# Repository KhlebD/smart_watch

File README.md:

# ESP32-S3 Smartwatch

A DIY smartwatch built from scratch around the ESP32-S3-Zero, with custom PCBs, a round touch display running LVGL, health and environment sensors, and a custom Android companion app.

https://github.com/user-attachments/assets/0c07c2c6-404b-4337-90d6-0c7b8de9bd92

## Features

- Watch face with time, date, battery and BLE status
- Step counter, heart rate, altitude and temperature
- Phone notifications, music controls and run tracking over BLE
- Hebrew (right-to-left) text support
- Wake on wrist motion and swipe navigation

## Hardware

The electronics are split over two round 48 mm PCBs designed in KiCad (in [`hardware/`](hardware/)), and the case is a parametric OpenSCAD model (in [`case/`](case/)). 

## Firmware

Arduino on PlatformIO, with LVGL 8.3.11, LovyanGFX and NimBLE. The watch talks to the phone using the Gadgetbridge / Bangle.js JSON protocol.

To build: open the project in PlatformIO, select the `esp32-s3-zero` environment, then build and upload over USB.

## Companion app

A custom Kotlin Android app syncs the time, forwards notifications, controls music and receives run data. [github/co](https://github.com/KhlebD/watch_app)

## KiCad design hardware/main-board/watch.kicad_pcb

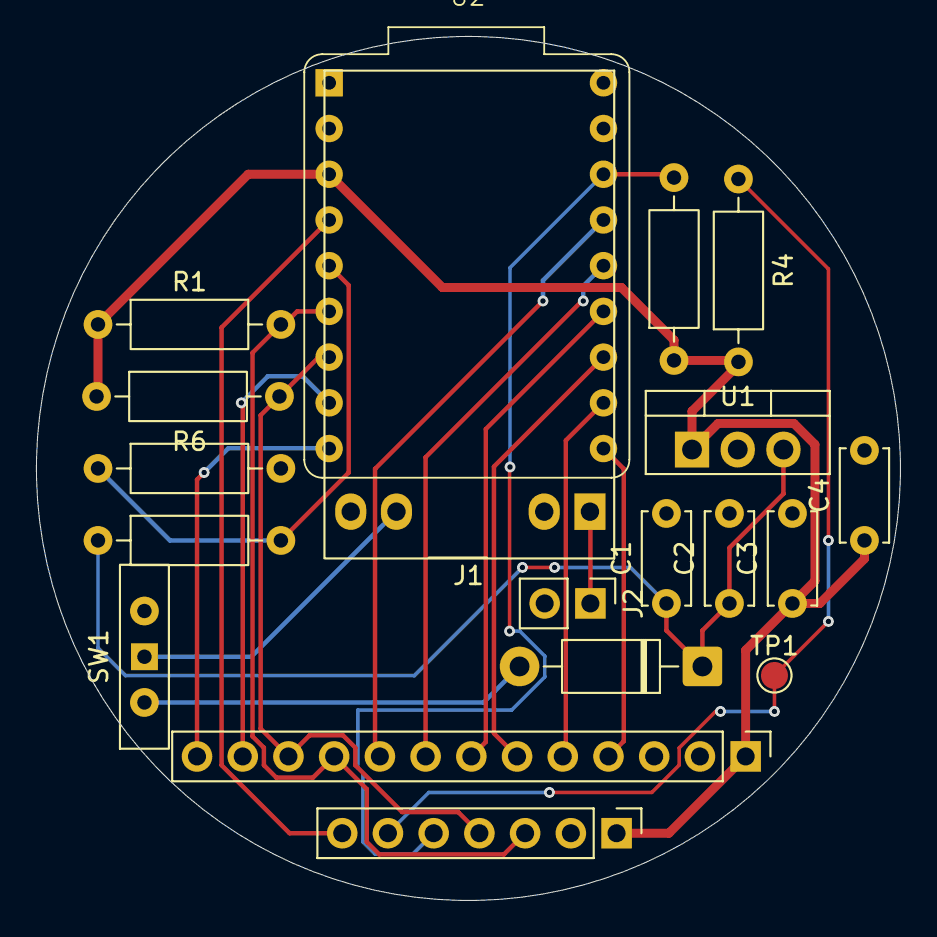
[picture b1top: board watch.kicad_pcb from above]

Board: 2 copper layers, 48.0 x 48.0 mm, 19 parts (0 on the bottom side), 20 nets.

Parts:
C1, C3: 100nF; C_Disc_D5.0mm_W2.5mm_P5.00mm
C2, C4: 10µF; C_Disc_D5.0mm_W2.5mm_P5.00mm
D1: 1N5817; D_DO-41_SOD81_P10.16mm_Horizontal
J1: TP4056; FanPinHeader_1x04_P2.54mm_Vertical
J2: Battery; PinHeader_1x02_P2.54mm_Vertical
J3: To-Sensor-Board; PinHeader_1x07_P2.54mm_Vertical
J5: GC9A01+CST816S; PinHeader_1x13_P2.54mm_Vertical
R1, R2, R3, R4: 5.1k; R_Axial_DIN0207_L6.3mm_D2.5mm_P10.16mm_Horizontal
R5, R6: 100k; R_Axial_DIN0207_L6.3mm_D2.5mm_P10.16mm_Horizontal
SW1: SS12D00; SW_Slide-03_Wuerth-WS-SLTV_10x2.5x6.4_P2.54mm
TP1: TestPoint; TestPoint_Pad_D1.5mm
U1: HT7333; TO-220-3_Vertical
U2: ESP32-S3-Zero; Waveshare-ESP32-S3-Zero

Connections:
+3.3V: C3.1, C4.1, J3.1, J5.1 (VCC), R1.1, R2.1, R3.1, R4.1, U1.1 (GND), U2.3 (3V3(OUT))
/SCL: J3.4, J5.11 (TP_SCL), R2.2, U2.7 (GPIO4)
/SDA: J3.3, J5.10 (TP_SDA), R1.2, U2.6 (GPIO3)
GND: C1.2, C2.2, C3.2, C4.2, J1.2 (BAT-), J1.4 (OUT-), J2.2 (BAT-), J3.2, J5.2 (GND), R6.2, U1.2 (VO), U2.2 (GND)
unnamed: D1.2 (A), SW1.2 (OUT_POS)
unnamed: C1.1, C2.1, D1.1 (K), R5.1, U1.3 (VI)
unnamed: J1.1 (BAT+), J2.1 (BAT+)
unnamed: J1.3 (OUT+), SW1.1 (SWITCHED_PWR)
unnamed: J3.5, R3.2, U2.16 (GPIO13)
unnamed: J3.6, R4.2, TP1.1 (1_1)
unnamed: J3.7, U2.4 (GPIO1)
unnamed: J5.9 (LCD_BL), U2.15 (GPIO12)
unnamed: J5.6 (LCD_CS), U2.12 (GPIO9)
unnamed: J5.7 (LCD_DC), U2.13 (GPIO10)
unnamed: J5.8 (LCD_RST), U2.14 (GPIO11)
unnamed: J5.4 (MOSI), U2.10 (GPIO7)
unnamed: J5.5 (SCLK), U2.11 (GPIO8)
unnamed: J5.12 (TP_INT), U2.8 (GPIO5)
unnamed: J5.13 (TP_RST), U2.9 (GPIO6)
unnamed: R5.2, R6.1, U2.5 (GPIO2)

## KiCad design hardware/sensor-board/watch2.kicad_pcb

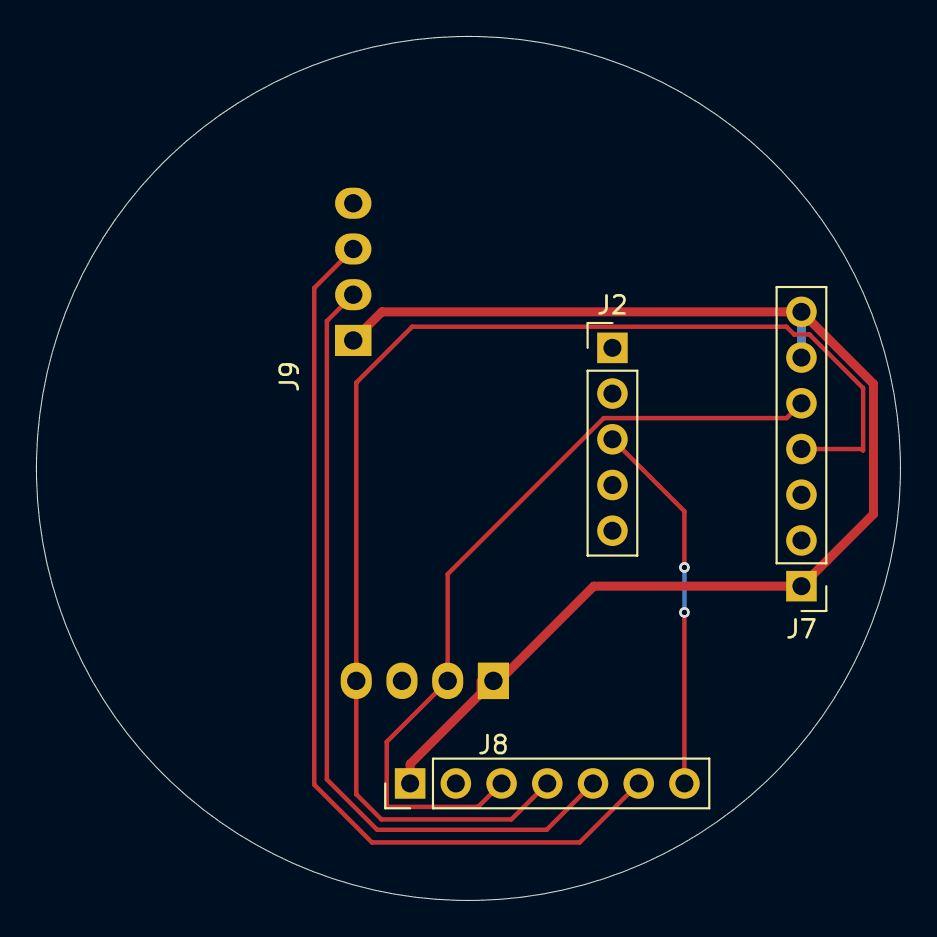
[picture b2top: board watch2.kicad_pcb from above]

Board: 2 copper layers, 48.0 x 48.0 mm, 5 parts (0 on the bottom side), 7 nets.

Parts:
J1: To-Main-Board; PinHeader_1x07_P2.54mm_Vertical
J2: BMI160L; PinHeader_1x05_P2.54mm_Vertical
J7: BMI160R; PinHeader_1x07_P2.54mm_Vertical
J8: BMP280/AHT20; FanPinHeader_1x04_P2.54mm_Vertical
J9: MAX30102; FanPinHeader_1x04_P2.54mm_Vertical

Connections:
+3V3: J1.1 (3.3V), J7.1 (VIN), J7.6 (CS), J7.7 (SA0), J8.1 (VDD), J9.1 (VIN)
GND: J1.2 (GND), J7.3 (GND), J8.3 (GND), J9.4 (GND)
unnamed: J1.7 (BMI160_INT), J2.3 (INT1_3)
unnamed: J1.6 (HR_SCL), J9.3 (SCL)
unnamed: J1.5 (HR_SDA), J9.2 (SDA)
unnamed: J1.4 (SCL), J7.4 (SCL), J8.4 (SCL)
unnamed: J1.3 (SDA), J7.5 (SDA), J8.2 (SDA)

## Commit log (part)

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2026-06-28 Touch thingy fixed
2026-06-28 Color fixes
2026-06-28 RTC change
